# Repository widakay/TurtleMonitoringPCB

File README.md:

# TurtleMonitoringPCB

This repo has moved here: https://github.com/leatherback-monitoring/SensorPCB

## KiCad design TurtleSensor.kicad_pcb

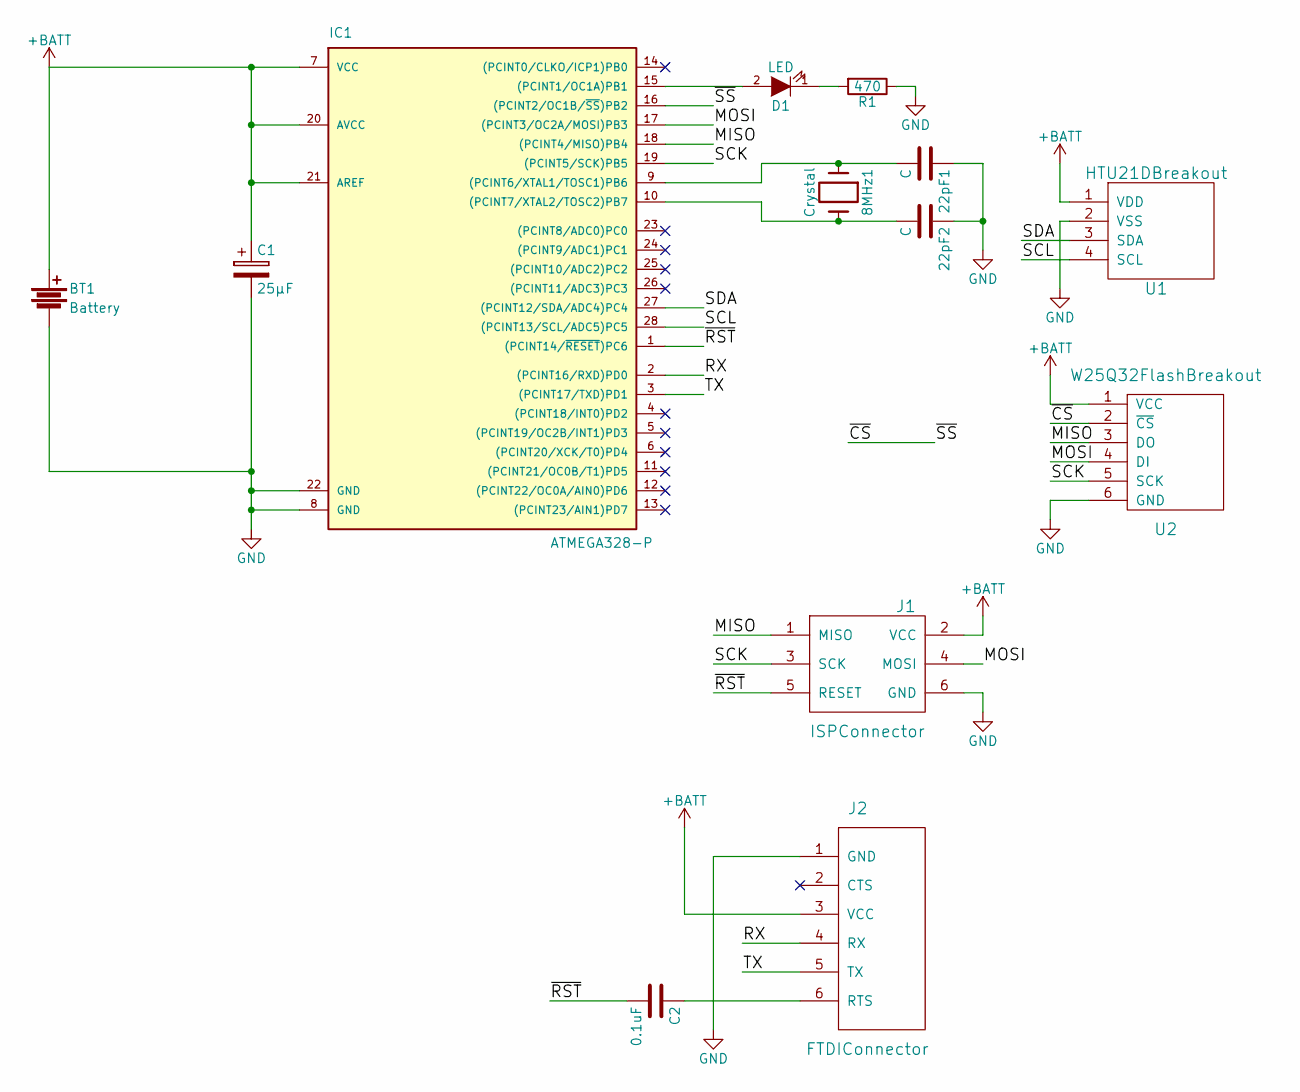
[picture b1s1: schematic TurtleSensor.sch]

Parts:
8MHz1: Crystal; Crystal_HC49-U_Vertical
22pF1, 22pF2: C; C_Disc_D3_P2.5
BT1: Battery; Socket_Strip_Straight_1x02
C1: 25µF; C_Radial_D5_L11_P2.5
C2: 0.1uF; C_Disc_D3_P2.5
D1: LED; LED-5MM
IC1: ATMEGA328-P; DIP-28_W7.62mm
J1: ISPConnector; Socket_Strip_Straight_2x03
J2: FTDIConnector; Socket_Strip_Angled_1x06
R1: 470; Resistor_Horizontal_RM10mm
U1: HTU21DBreakout; Socket_Strip_Straight_1x04
U2: W25Q32FlashBreakout; Socket_Strip_Straight_1x06

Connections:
+BATT: BT1.1, C1.1, IC1.7 (VCC), IC1.20 (AVCC), IC1.21 (AREF), J1.2 (VCC), J2.3 (VCC), U1.1 (VDD), U2.1 (VCC)
/MISO: IC1.18 ((PCINT4/MISO)PB4), J1.1 (MISO), U2.3 (DO)
/MOSI: IC1.17 ((PCINT3/OC2A/MOSI)PB3), J1.4 (MOSI), U2.4 (DI)
/RX: IC1.2 ((PCINT16/RXD)PD0), J2.4 (RX)
/SCK: IC1.19 ((PCINT5/SCK)PB5), J1.3 (SCK), U2.5 (SCK)
/SCL: IC1.28 ((PCINT13/SCL/ADC5)PC5), U1.4 (SCL)
/SDA: IC1.27 ((PCINT12/SDA/ADC4)PC4), U1.3 (SDA)
/TX: IC1.3 ((PCINT17/TXD)PD1), J2.5 (TX)
/~CS: IC1.16 ((PCINT2/OC1B/~SS~)PB2), U2.2 (~CS)
/~RST: C2.2, IC1.1 ((PCINT14/~RESET~)PC6), J1.5 (RESET)
GND: 22pF1.1, 22pF2.1, BT1.2, C1.2, IC1.8 (GND), IC1.22 (GND), J1.6 (GND), J2.1 (GND), R1.1, U1.2 (VSS), U2.6 (GND)
unnamed: 8MHz1.1, 22pF1.2, IC1.9 ((PCINT6/XTAL1/TOSC1)PB6)
unnamed: 8MHz1.2, 22pF2.2, IC1.10 ((PCINT7/XTAL2/TOSC2)PB7)
unnamed: C2.1, J2.6 (RTS)
unnamed: D1.1 (K), R1.2
unnamed: D1.2 (A), IC1.15 ((PCINT1/OC1A)PB1)

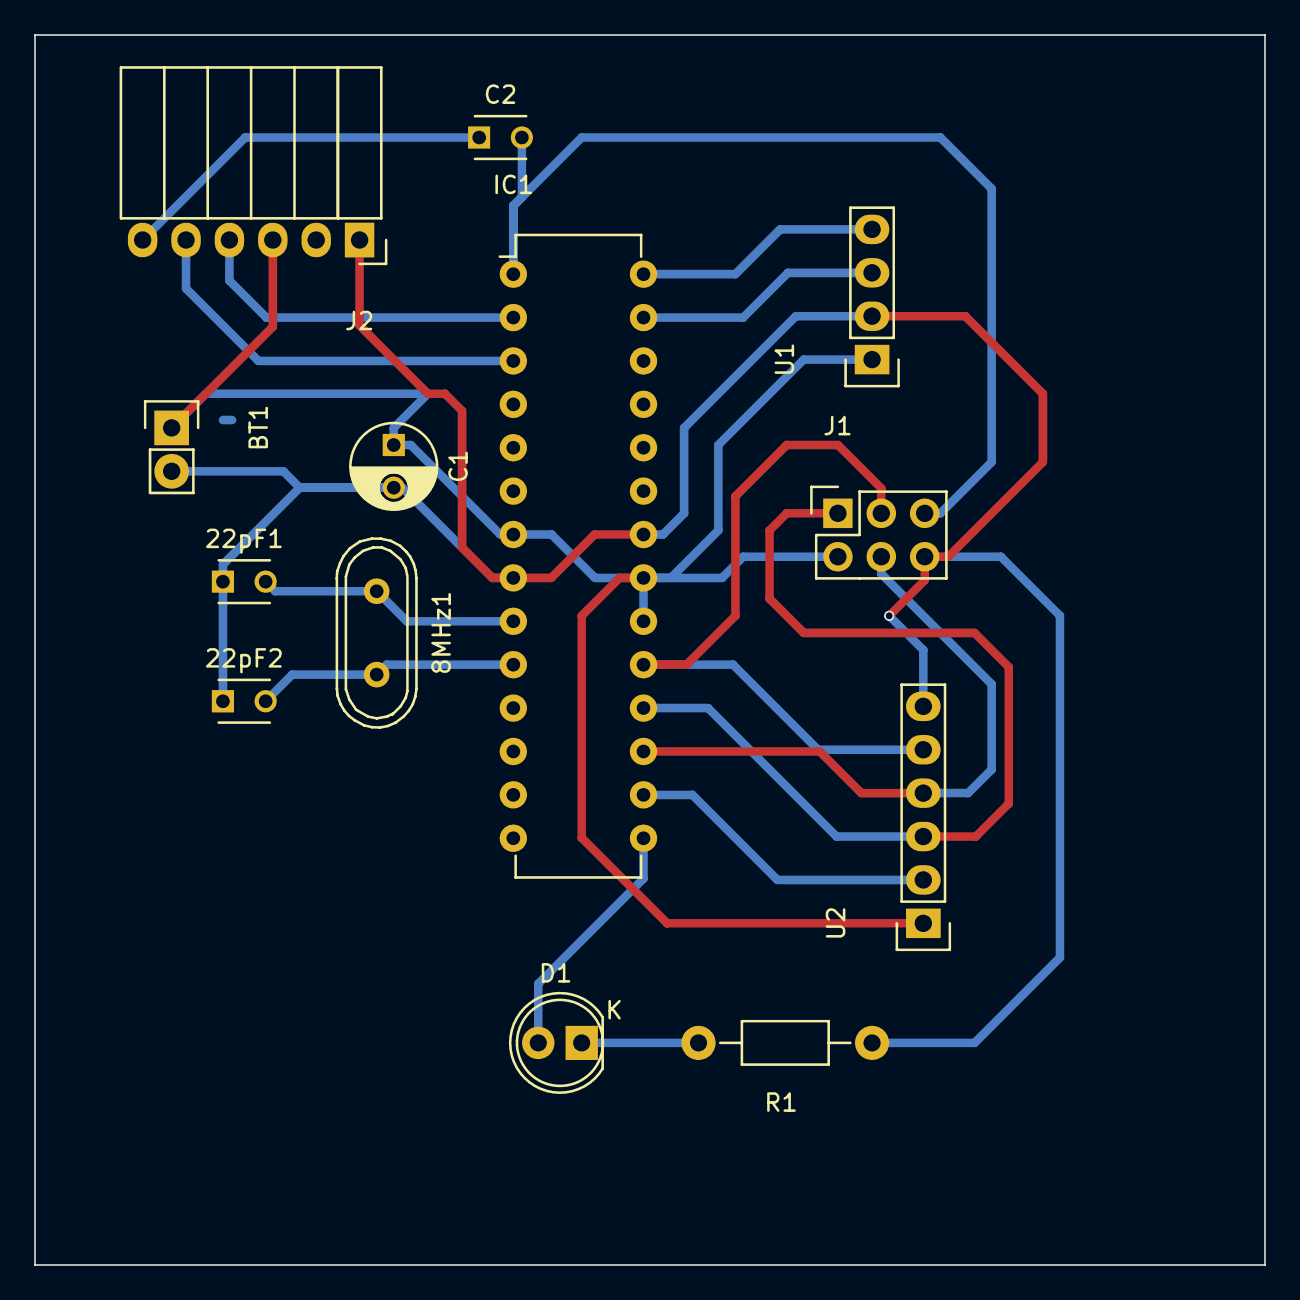
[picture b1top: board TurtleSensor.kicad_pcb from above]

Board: 2 copper layers, 72.0 x 72.0 mm, 13 parts (0 on the bottom side), 16 nets.

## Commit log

2016-02-14 before annotation
2016-02-19 first starts of a layout
2016-02-19 started routing
2016-02-19 before new pcb
2016-02-21 routed pcb rev 0.1
2016-02-21 update component positioning
2016-02-28 pcb cut
2016-02-28 updated gitignore
2016-03-06 swapped layers and added programming header
